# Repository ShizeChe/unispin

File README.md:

<h1 align="center">Unispin</h1>
<p align="center">A unified quantum control platform for quantum dot spin qubits</p>

Overview
========
Unispin is a unified quantum control platform designed specifically for quantum dot spin qubits. Its goal is to reduce control stack complexity and cost while improving performance by integrating all the requried control resources onto a single FPGA. With the two custom PCBs (FMC breakout board and low-noise DAC board), the current configuration has:

* 24x bias DC channels (AD5791BRUZ)
* 6x RF IQ pairs for further analog upconversion
* 2x singled-ended RF channels and 2x ADC channels for lockin-in measurement
* 2x singled-ended fast DC channels

Each signal and measurement channel has its own dedicated, fully-pipelined control core. Each core can be programmed to iteratively executes a sequence of custom assembly instructions with cycle-precise timing. The annotated pulse experiment assembly program and waveform below demonstrates this execution model.

```text
.program rf0                 # program for RF channel 0
.fnco 10MHz                  # NCO is 10MHz
.repeat 100                  # repeats 100 times
    idl t=19us (arm)         # idle for 19us
    ply phs=0 t=12ns (t+8ns) # play the NCO tone for 12ns (increment the pulse duration by 8ns every iteration)
    idl t=12us               # idle for 12us

.program dc0                 # program for DC channel 0
.repeat 100                  # this program repeats 100 times
    lvl v=0 t=2us (arm)      # output 0V for 2us
    lvl v=1 t=15us           # output 1V for 15us
    lvl v=2 t=2us            # output 2V for 2us
    idl t=12ns (t+8ns)       # idle for 12ns (increment the idle duration by 8ns every iteration)
    lvl v=1 t=10us           # output 1V for 10us
    lvl v=0 t=2us            # output 0V for 2us

.program li0                 # program for LI (lock-in) channel 0
.repeat 100                  # this program repeats 100 times
    idl t=19us (arm)         # idle for 19us
    idl t=12ns (t+8ns)       # idle for 12ns (increment the idle duration by 8ns every iteration)
    sam n=1000 t=10us        # sample 1000 samples spanning 10us
    idl t=2us                # idle for 2us

.launch rf0 dc0 li0          # launch RF channel 0, DC channel 0, LI channel 0 
```

## Project Status
The project currently has three parts:
* RTL design, along with testbenches and some formal properties used for verification (under rtl)
* PCB design for the 24 bias DC channels, along with assembly instrctions (under pcb)
* Assembler for compiling and executing the custom assembly programs (under asm)

This project is currently under active development. The RTL design, PCB design, and assembler may continue to evolve as functionality is validated experimentally and the system is further refined. More detailed documentation and user guides will be added after real-device experiments.

## Building the rtl design project and bistream in Vivado
```bash
# clone repo
git clone "repo-url"

# go to the synthesis folder
cd unispin/rtl/synth

# build in vivado
vivado -script proj.tcl &
```
Note that proj.tcl only builds the project. Click generate bitstream in vivado to build the bitstream.

## Building the simulator (requires VCS+Verdi)
This simulator is our go-to method to visualize the full-system waveforms. It incorporates all the channels and cores and have simulated DAC and ADC modules for directly visualizing analog waveforms. It simulates AXI memory operations by accepting address and data through a socket interface, the received address and data are then written to the sequencer through its AXI interface.

Build the simulator. 
```bash
# assume we are in the top level of the cloned repo

# go to the rtl folder
cd unispin/rtl

# build the simulator (requires VCS)
make
```
This will create a simulator executable under rtl.

Execute the simulator in Verdi.
```bash
./simulator -gui -do sim/wv.tcl &
```

This will open up Verdi and load the waveforms. It will listen for connections and read address and data once running. Verdi can stop it at anytime to examine waveforms.

## Building the assembler
```bash
# assume we are in the top level of the cloned repo

# go to the asm folder
cd asm

# build the assmebler
make
```
This will create an executable named "squish" under asm.

Example assembling a .asm file and send to the simulator to visualize exection (with simulator running).
```bash
./squish -s -f ../exp/hahn_echo.asm
```

## Petalinux
A Petalinux OS can be built to interface with the cores in FPGA. os/petalinux-steps.md describes the steps we took to build a bootable image with an uio driver for each core.

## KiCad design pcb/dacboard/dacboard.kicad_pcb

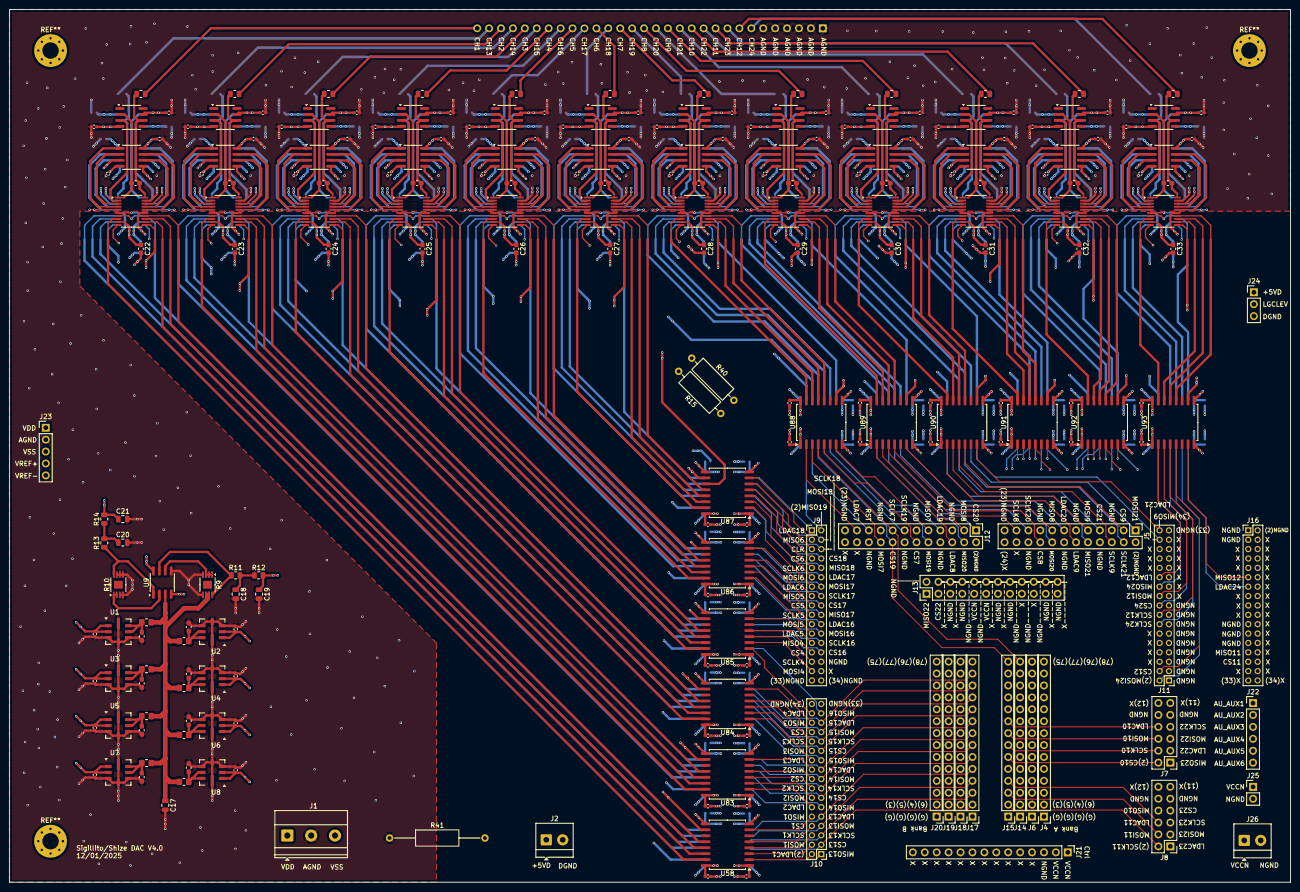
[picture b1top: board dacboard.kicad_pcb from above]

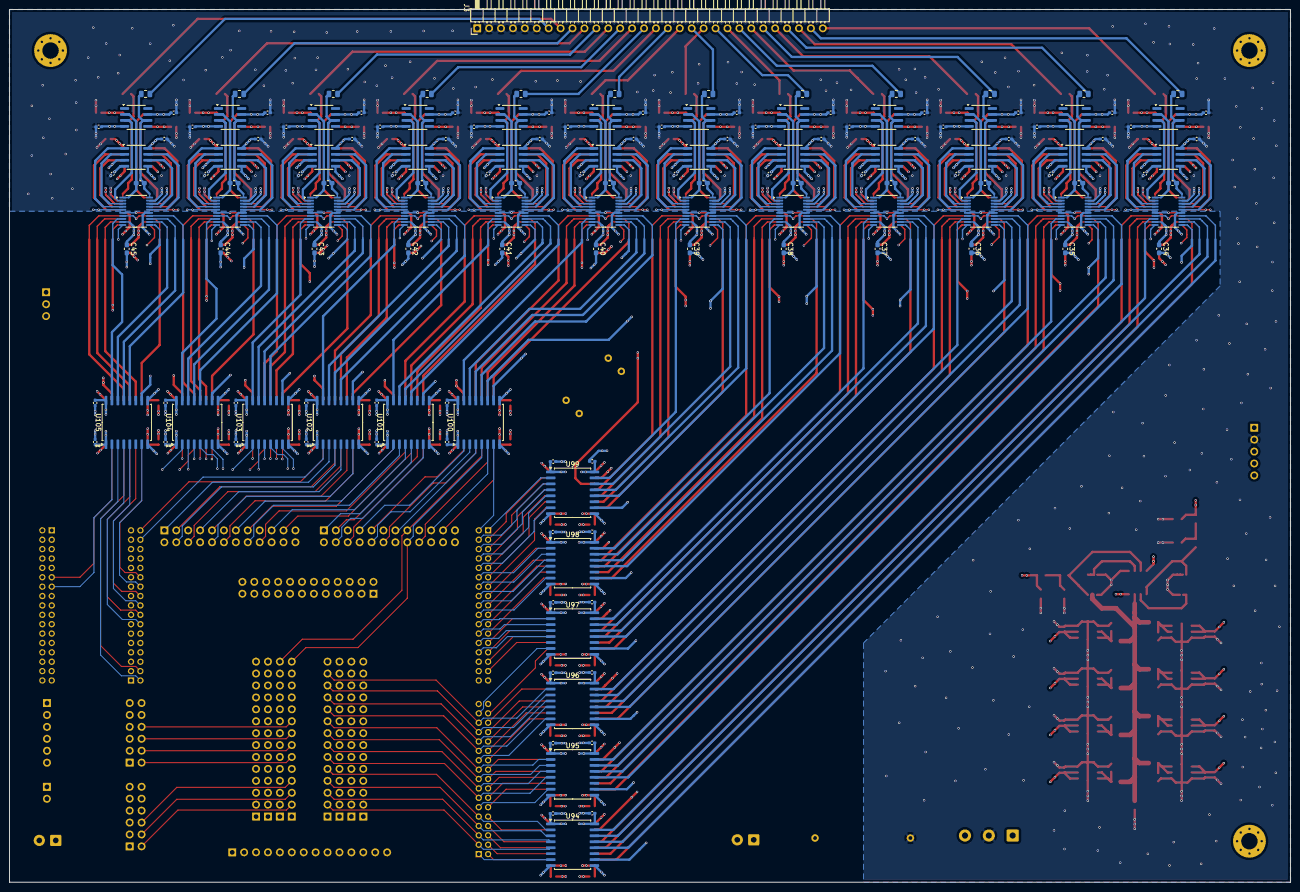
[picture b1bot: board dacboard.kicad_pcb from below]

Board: 14 copper layers, 273.0 x 186.0 mm, 385 parts (157 on the bottom side), 467 nets.

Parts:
C1, C3, C5, C7, C9, C11, C13, C15, C72, C73, C74, C75, C76, C77, C78, C79, C80, C81, C82, C83, C84, C85, C86, C87, C88, C89, C90, C91, C92, C93, C94, C95, C96, C97, C98, C99, C100, C101, C102, C103, C104, C105, C106, C107, C108, C109, C110, C111, C112, C113, C114, C115, C116, C117, C118, C119: 0.1uF; C_0402_1005Metric_Pad0.74x0.62mm_HandSolder
C2, C4, C6, C8, C10, C12, C14, C16, C22, C23, C24, C25, C26, C27, C28, C29, C30, C31, C32, C33, C34, C35, C36, C37, C38, C39, C40, C41, C42, C43, C44, C45: 10uF; C_0603_1608Metric_Pad1.08x0.95mm_HandSolder
C17, C18, C19, C20, C21: C; C_0805_2012Metric
C46, C71, C120, C121, C122, C123, C124, C125, C126, C127, C128, C129, C130, C131, C132, C133, C134, C135, C136, C137, C138, C139, C140, C141, C142, C143, C144, C145, C146, C147, C148, C149, C150, C151, C152, C153, C154, C155, C156, C157, C158, C159, C160, C161, C162, C163, C164, C165, C166, C167, C168, C169, C170, C171, C172, C173, C174, C175, C176, C177, C178, C179, C180, C181, C182, C183, C184, C185, C186, C187, C188, C189, C190, C191, C192, C193, C194, C195, C196, C197, C198, C199, C200, C201, C202, C203, C204, C205, C206, C207, C208, C209, C210, C211, C212, C213: C; C_0402_1005Metric_Pad0.74x0.62mm_HandSolder
C47, C48, C49, C50, C51, C52, C53, C54, C55, C56, C57, C58, C59, C60, C61, C62, C63, C64, C65, C66, C67, C68, C69, C70: 10pF; C_0603_1608Metric_Pad1.08x0.95mm_HandSolder
J1: Screw_Terminal_01x03; TerminalBlock_Phoenix_MKDS-1,5-3-5.08_1x03_P5.08mm_Horizont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
J2, J26: Screw_Terminal_01x02; TerminalBlock_4Ucon_1x02_P3.50mm_Horizontal
J3: Conn_01x30_Socket; PinHeader_1x30_P2.54mm_Horizontal
J4, J6, J14, J15, J17, J18, J19, J20, J21: Conn_01x14; PinHeader_1x14_P2.54mm_Vertical
J5, J12, J13: Conn_02x12_Odd_Even; PinHeader_2x12_P2.54mm_Vertical
J7, J8: Conn_02x06_Odd_Even; PinHeader_2x06_P2.54mm_Vertical
J9, J10, J11, J16: Conn_02x17_Odd_Even; PinHeader_2x17_P2.00mm_Vertical
J22: Conn_01x06; PinHeader_1x06_P2.54mm_Vertical
J23: Conn_01x05; PinHeader_1x05_P2.54mm_Vertical
J24: Conn_01x03; PinHeader_1x03_P2.54mm_Vertical
J25: Conn_01x02; PinHeader_1x02_P2.54mm_Vertical
R1, R2, R3, R4, R5, R6, R7, R8: 32.4ohm; R_0805_2012Metric_Pad1.20x1.40mm_HandSolder
R9, R10: LT5400BCMS8E-7_PBF; MSOP-8-1EP_3x3mm_P0.65mm_EP1.68x1.88mm
R11, R12, R13, R14, R16, R17, R18, R19, R20, R21, R22, R23, R24, R25, R26, R27, R28, R29, R30, R31, R32, R33, R34, R35, R36, R37, R38, R39: R_US; R_0805_2012Metric
R15, R40: R_US; R_Axial_DIN0309_L9.0mm_D3.2mm_P12.70mm_Horizontal
R41: R_US; R_Axial_DIN0309_L9.0mm_D3.2mm_P20.32mm_Horizontal
U1, U2, U3, U4, U5, U6, U7, U8: LTC6655CHMS8-2.5_PBF; Analog_LCC-8_5x5mm_P1.27mm
U9, U11, U12, U14, U16, U18, U20, U22, U23, U24, U25, U30, U31, U34, U35, U36, U37, U42, U43, U46, U47, U48, U49, U54, U55: AD8676xR; SOIC-8_3.9x4.9mm_P1.27mm
U10, U13, U15, U17, U19, U21, U26, U27, U28, U29, U32, U33, U38, U39, U40, U41, U44, U45, U50, U51, U52, U53, U56, U57: AD5791BRUZ; TSSOP-20_4.4x6.5mm_P0.65mm
U58, U83, U84, U85, U86, U87, U88, U89, U90, U91, U92, U93, U94, U95, U96, U97, U98, U99, U100, U101, U102, U103, U104, U105: ISO6761FQDWRQ1; SOIC-16W_7.5x10.3mm_P1.27mm
U59, U60, U61, U62, U63, U64, U65, U66, U67, U68, U69, U70, U71, U72, U73, U74, U75, U76, U77, U78, U79, U80, U81, U82: AD8675ARZ; SOIC-8_3.9x4.9mm_P1.27mm

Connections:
+5VD: C22.1, C23.1, C24.1, C25.1, C26.1, C27.1, C28.1, C29.1, C30.1, C31.1, C32.1, C33.1, C34.1, C35.1, C36.1, C37.1, C38.1, C39.1, C40.1, C41.1, C42.1, C43.1, C44.1, C45.1, C73.2, C75.2, C77.2, C81.2, C82.2, C83.2, C87.2, C88.2, C89.2, C93.2, C94.2, C95.2, C99.2, C100.2, C101.2, C105.2, C106.2, C107.2, C111.2, C112.2, C113.2, C117.2, C118.2, C119.2, J2.1, J24.1, R15.1, U10.9 (VCC), U13.9 (VCC), U15.9 (VCC), U17.9 (VCC), U19.9 (VCC), U21.9 (VCC), U26.9 (VCC), U27.9 (VCC), U28.9 (VCC), U29.9 (VCC), U32.9 (VCC), U33.9 (VCC), U38.9 (VCC), U39.9 (VCC), U40.9 (VCC), U41.9 (VCC), U44.9 (VCC), U45.9 (VCC), U50.9 (VCC), U51.9 (VCC), U52.9 (VCC), U53.9 (VCC), U56.9 (VCC), U57.9 (VCC), U58.16 (VCC2), U83.16 (VCC2), U84.16 (VCC2), U85.16 (VCC2), U86.16 (VCC2), U87.16 (VCC2), U88.16 (VCC2), U89.16 (VCC2), U90.16 (VCC2), U91.16 (VCC2), U92.16 (VCC2), U93.16 (VCC2), U94.16 (VCC2), U95.16 (VCC2), U96.16 (VCC2), U97.16 (VCC2), U98.16 (VCC2), U99.16 (VCC2), U100.16 (VCC2), U101.16 (VCC2), U102.16 (VCC2), U103.16 (VCC2), U104.16 (VCC2), U105.16 (VCC2)
AGND: C1.2, C2.2, C3.2, C4.2, C5.2, C6.2, C7.2, C8.2, C9.2, C10.2, C11.2, C12.2, C13.2, C14.2, C15.2, C16.2, C17.2, C18.2, C19.2, C20.2, C21.2, C46.2, C71.2, C120.2, C121.2, C122.2, C123.2, C124.2, C125.2, C126.2, C127.2, C128.2, C129.2, C130.2, C131.2, C132.2, C133.2, C134.2, C135.2, C136.2, C137.2, C138.2, C139.2, C140.2, C141.2, C142.2, C143.2, C144.2, C145.2, C146.2, C147.2, C148.2, C149.2, C150.2, C151.2, C152.2, C153.2, C154.2, C155.2, C156.2, C157.2, C158.2, C159.2, C160.2, C161.2, C162.2, C163.2, C164.2, C165.2, C166.2, C167.2, C168.2, C169.2, C170.2, C171.2, C172.2, C173.2, C174.2, C175.2, C176.2, C177.2, C178.2, C179.2, C180.2, C181.2, C182.2, C183.2, C184.2, C185.2, C186.2, C187.2, C188.2, C189.2, C190.2, C191.2, C192.2, C193.2, C194.2, C195.2, C196.2, C197.2, C198.2, C199.2, C200.2, C201.2, C202.2, C203.2, C204.2, C205.2, C206.2, C207.2, C208.2, C209.2, C210.2, C211.2, C212.2, C213.2, J1.2, J3.1, J3.2, J3.3, J3.4, J3.5, J3.6, J23.2, R9.4, R9.5, R10.3, R10.4, R10.5, R10.6, R10.7, R41.1, U1.3 (GND), U1.4 (GND__1), U1.5 (GND__2), U1.8 (GND__3), U2.3 (GND), U2.4 (GND__1), U2.5 (GND__2), U2.8 (GND__3), U3.3 (GND), U3.4 (GND__1), U3.5 (GND__2), U3.8 (GND__3), U4.3 (GND), U4.4 (GND__1), U4.5 (GND__2), U4.8 (GND__3), U5.3 (GND), U5.4 (GND__1), U5.5 (GND__2), U5.8 (GND__3), U6.3 (GND), U6.4 (GND__1), U6.5 (GND__2), U6.8 (GND__3), U7.3 (GND), U7.4 (GND__1), U7.5 (GND__2), U7.8 (GND__3), U8.3 (GND), U8.4 (GND__1), U8.5 (GND__2), U8.8 (GND__3), U9.5 (+), U10.19 (AGND), U13.19 (AGND), U15.19 (AGND), U17.19 (AGND), U19.19 (AGND), U21.19 (AGND), U26.19 (AGND), U27.19 (AGND), U28.19 (AGND), U29.19 (AGND), U32.19 (AGND), U33.19 (AGND), U38.19 (AGND), U39.19 (AGND), U40.19 (AGND), U41.19 (AGND), U44.19 (AGND), U45.19 (AGND), U50.19 (AGND), U51.19 (AGND), U52.19 (AGND), U53.19 (AGND), U56.19 (AGND), U57.19 (AGND)
AU_AUX1: J14.6, J22.1
AU_AUX2: J15.5, J22.2
AU_AUX3: J4.5, J22.3
AU_AUX4: J4.4, J22.4
AU_AUX5: J4.3, J22.5
AU_AUX6: J4.2, J22.6
BUF1_VOUT: J3.30, R16.2
BUF2_VOUT: J3.28, R17.2
BUF3_VOUT: J3.26, R18.2
BUF4_VOUT: J3.24, R19.2
BUF5_VOUT: J3.22, R20.2
BUF6_VOUT: J3.20, R21.2
BUF7_VOUT: J3.18, R22.2
BUF8_VOUT: J3.16, R23.2
BUF9_VOUT: J3.14, R24.2
BUF10_VOUT: J3.12, R25.2
BUF11_VOUT: J3.10, R26.2
BUF12_VOUT: J3.8, R27.2
BUF13_VOUT: J3.29, R28.2
BUF14_VOUT: J3.27, R29.2
BUF15_VOUT: J3.25, R30.2
BUF16_VOUT: J3.23, R31.2
BUF17_VOUT: J3.21, R32.2
BUF18_VOUT: J3.19, R33.2
BUF19_VOUT: J3.17, R34.2
BUF20_VOUT: J3.15, R35.2
BUF21_VOUT: J3.13, R36.2
BUF22_VOUT: J3.11, R37.2
BUF23_VOUT: J3.9, R38.2
BUF24_VOUT: J3.7, R39.2
CLR_N: U10.7 (*CLR), U13.7 (*CLR), U15.7 (*CLR), U17.7 (*CLR), U19.7 (*CLR), U21.7 (*CLR), U26.7 (*CLR), U27.7 (*CLR), U28.7 (*CLR), U29.7 (*CLR), U32.7 (*CLR), U33.7 (*CLR), U38.7 (*CLR), U39.7 (*CLR), U40.7 (*CLR), U41.7 (*CLR), U44.7 (*CLR), U45.7 (*CLR), U50.7 (*CLR), U51.7 (*CLR), U52.7 (*CLR), U53.7 (*CLR), U56.7 (*CLR), U57.7 (*CLR), U87.11 (OUTE)
CLR_N_ALLCH: J9.5, J20.13, U87.6 (INE)
CS_N_CH1: J10.8, J18.5, U58.5 (IND)
CS_N_CH2: J10.18, J18.9, U83.5 (IND)
CS_N_CH3: J10.28, J18.13, U84.5 (IND)
CS_N_CH4: J9.27, J20.4, U85.5 (IND)
CS_N_CH5: J9.17, J20.8, U86.5 (IND)
CS_N_CH6: J9.7, J20.12, U87.5 (IND)
CS_N_CH7: J4.14, J12.12, U88.5 (IND)
CS_N_CH8: J5.18, J15.11, U89.5 (IND)
CS_N_CH9: J4.9, J5.3, U90.5 (IND)
CS_N_CH10: J7.2, J15.6, U91.5 (IND)
CS_N_CH11: J4.6, J16.29, U92.5 (IND)
CS_N_CH12: J6.3, J11.4, U93.5 (IND)
CS_N_CH13: J10.3, J17.2, U94.5 (IND)
CS_N_CH14: J10.13, J17.6, U95.5 (IND)
CS_N_CH15: J10.23, J17.10, U96.5 (IND)
CS_N_CH16: J9.28, J19.2, U97.5 (IND)
CS_N_CH17: J9.18, J19.6, U98.5 (IND)
CS_N_CH18: J9.8, J19.10, U99.5 (IND)
CS_N_CH19: J12.16, J15.14, U100.5 (IND)
CS_N_CH20: J12.1, J14.12, U101.5 (IND)
CS_N_CH21: J5.7, J14.10, U102.5 (IND)
CS_N_CH22: J13.3, J14.13, U103.5 (IND)
CS_N_CH23: J8.7, J14.5, U104.5 (IND)
CS_N_CH24: J6.6, J11.18, U105.5 (IND)
DAC1_INV: C47.1, U10.1 (INV), U59.2 (IN-)
DAC1_LDAC_N: U10.8 (*LDAC), U58.15 (OUTA)
DAC1_RFB: C47.2, R16.1, U10.20 (RFB), U59.6 (OUT)
DAC1_SCLK: U10.13 (SCLK), U58.13 (OUTC)
DAC1_SDIN: U10.12 (SDIN), U58.14 (OUTB)
DAC1_SDO: U10.11 (SDO), U58.10 (INF)
DAC1_SYNC_N: U10.14 (*SYNC), U58.12 (OUTD)
DAC1_VOUT: U10.2 (VOUT), U59.3 (IN+)
DAC2_INV: C48.1, U13.1 (INV), U60.2 (IN-)
DAC2_LDAC_N: U13.8 (*LDAC), U83.15 (OUTA)
DAC2_RFB: C48.2, R17.1, U13.20 (RFB), U60.6 (OUT)
DAC2_SCLK: U13.13 (SCLK), U83.13 (OUTC)
DAC2_SDIN: U13.12 (SDIN), U83.14 (OUTB)
DAC2_SDO: U13.11 (SDO), U83.10 (INF)
DAC2_SYNC_N: U13.14 (*SYNC), U83.12 (OUTD)
DAC2_VOUT: U13.2 (VOUT), U60.3 (IN+)
DAC3_INV: C49.1, U15.1 (INV), U61.2 (IN-)
DAC3_LDAC_N: U15.8 (*LDAC), U84.15 (OUTA)
DAC3_RFB: C49.2, R18.1, U15.20 (RFB), U61.6 (OUT)
DAC3_SCLK: U15.13 (SCLK), U84.13 (OUTC)
DAC3_SDIN: U15.12 (SDIN), U84.14 (OUTB)
DAC3_SDO: U15.11 (SDO), U84.10 (INF)
DAC3_SYNC_N: U15.14 (*SYNC), U84.12 (OUTD)
DAC3_VOUT: U15.2 (VOUT), U61.3 (IN+)
DAC4_INV: C50.1, U17.1 (INV), U62.2 (IN-)
DAC4_LDAC_N: U17.8 (*LDAC), U85.15 (OUTA)
DAC4_RFB: C50.2, R19.1, U17.20 (RFB), U62.6 (OUT)
DAC4_SCLK: U17.13 (SCLK), U85.13 (OUTC)
DAC4_SDIN: U17.12 (SDIN), U85.14 (OUTB)
DAC4_SDO: U17.11 (SDO), U85.10 (INF)
DAC4_SYNC_N: U17.14 (*SYNC), U85.12 (OUTD)
DAC4_VOUT: U17.2 (VOUT), U62.3 (IN+)
DAC5_INV: C51.1, U19.1 (INV), U63.2 (IN-)
DAC5_LDAC_N: U19.8 (*LDAC), U86.15 (OUTA)
DAC5_RFB: C51.2, R20.1, U19.20 (RFB), U63.6 (OUT)
DAC5_SCLK: U19.13 (SCLK), U86.13 (OUTC)
DAC5_SDIN: U19.12 (SDIN), U86.14 (OUTB)
DAC5_SDO: U19.11 (SDO), U86.10 (INF)
DAC5_SYNC_N: U19.14 (*SYNC), U86.12 (OUTD)
DAC5_VOUT: U19.2 (VOUT), U63.3 (IN+)
DAC6_INV: C52.1, U21.1 (INV), U64.2 (IN-)
DAC6_LDAC_N: U21.8 (*LDAC), U87.15 (OUTA)
DAC6_RFB: C52.2, R21.1, U21.20 (RFB), U64.6 (OUT)
DAC6_SCLK: U21.13 (SCLK), U87.13 (OUTC)
DAC6_SDIN: U21.12 (SDIN), U87.14 (OUTB)
DAC6_SDO: U21.11 (SDO), U87.10 (INF)
DAC6_SYNC_N: U21.14 (*SYNC), U87.12 (OUTD)
DAC6_VOUT: U21.2 (VOUT), U64.3 (IN+)
DAC7_INV: C53.1, U26.1 (INV), U65.2 (IN-)
DAC7_LDAC_N: U26.8 (*LDAC), U88.15 (OUTA)
DAC7_RFB: C53.2, R22.1, U26.20 (RFB), U65.6 (OUT)
DAC7_SCLK: U26.13 (SCLK), U88.13 (OUTC)
DAC7_SDIN: U26.12 (SDIN), U88.14 (OUTB)
DAC7_SDO: U26.11 (SDO), U88.10 (INF)
DAC7_SYNC_N: U26.14 (*SYNC), U88.12 (OUTD)
DAC7_VOUT: U26.2 (VOUT), U65.3 (IN+)
DAC8_INV: C54.1, U27.1 (INV), U66.2 (IN-)
DAC8_LDAC_N: U27.8 (*LDAC), U89.15 (OUTA)
DAC8_RFB: C54.2, R23.1, U27.20 (RFB), U66.6 (OUT)
DAC8_SCLK: U27.13 (SCLK), U89.13 (OUTC)
DAC8_SDIN: U27.12 (SDIN), U89.14 (OUTB)
DAC8_SDO: U27.11 (SDO), U89.10 (INF)
DAC8_SYNC_N: U27.14 (*SYNC), U89.12 (OUTD)
DAC8_VOUT: U27.2 (VOUT), U66.3 (IN+)
DAC9_INV: C55.1, U28.1 (INV), U67.2 (IN-)
DAC9_LDAC_N: U28.8 (*LDAC), U90.15 (OUTA)
DAC9_RFB: C55.2, R24.1, U28.20 (RFB), U67.6 (OUT)
DAC9_SCLK: U28.13 (SCLK), U90.13 (OUTC)
DAC9_SDIN: U28.12 (SDIN), U90.14 (OUTB)
DAC9_SDO: U28.11 (SDO), U90.10 (INF)
DAC9_SYNC_N: U28.14 (*SYNC), U90.12 (OUTD)
DAC9_VOUT: U28.2 (VOUT), U67.3 (IN+)
DAC10_INV: C56.1, U29.1 (INV), U68.2 (IN-)
DAC10_LDAC_N: U29.8 (*LDAC), U91.15 (OUTA)
DAC10_RFB: C56.2, R25.1, U29.20 (RFB), U68.6 (OUT)
DAC10_SCLK: U29.13 (SCLK), U91.13 (OUTC)
DAC10_SDIN: U29.12 (SDIN), U91.14 (OUTB)
DAC10_SDO: U29.11 (SDO), U91.10 (INF)
DAC10_SYNC_N: U29.14 (*SYNC), U91.12 (OUTD)
DAC10_VOUT: U29.2 (VOUT), U68.3 (IN+)
DAC11_INV: C57.1, U32.1 (INV), U69.2 (IN-)
DAC11_LDAC_N: U32.8 (*LDAC), U92.15 (OUTA)
DAC11_RFB: C57.2, R26.1, U32.20 (RFB), U69.6 (OUT)
DAC11_SCLK: U32.13 (SCLK), U92.13 (OUTC)
DAC11_SDIN: U32.12 (SDIN), U92.14 (OUTB)
DAC11_SDO: U32.11 (SDO), U92.10 (INF)
DAC11_SYNC_N: U32.14 (*SYNC), U92.12 (OUTD)
DAC11_VOUT: U32.2 (VOUT), U69.3 (IN+)
DAC12_INV: C58.1, U33.1 (INV), U70.2 (IN-)
DAC12_LDAC_N: U33.8 (*LDAC), U93.15 (OUTA)
DAC12_RFB: C58.2, R27.1, U33.20 (RFB), U70.6 (OUT)
DAC12_SCLK: U33.13 (SCLK), U93.13 (OUTC)
DAC12_SDIN: U33.12 (SDIN), U93.14 (OUTB)
DAC12_SDO: U33.11 (SDO), U93.10 (INF)
DAC12_SYNC_N: U33.14 (*SYNC), U93.12 (OUTD)
DAC12_VOUT: U33.2 (VOUT), U70.3 (IN+)
DAC13_INV: C59.1, U38.1 (INV), U71.2 (IN-)
DAC13_LDAC_N: U38.8 (*LDAC), U94.15 (OUTA)
DAC13_RFB: C59.2, R28.1, U38.20 (RFB), U71.6 (OUT)
DAC13_SCLK: U38.13 (SCLK), U94.13 (OUTC)
DAC13_SDIN: U38.12 (SDIN), U94.14 (OUTB)
DAC13_SDO: U38.11 (SDO), U94.10 (INF)
DAC13_SYNC_N: U38.14 (*SYNC), U94.12 (OUTD)
DAC13_VOUT: U38.2 (VOUT), U71.3 (IN+)
DAC14_INV: C60.1, U39.1 (INV), U72.2 (IN-)
DAC14_LDAC_N: U39.8 (*LDAC), U95.15 (OUTA)
DAC14_RFB: C60.2, R29.1, U39.20 (RFB), U72.6 (OUT)
DAC14_SCLK: U39.13 (SCLK), U95.13 (OUTC)
DAC14_SDIN: U39.12 (SDIN), U95.14 (OUTB)
DAC14_SDO: U39.11 (SDO), U95.10 (INF)
DAC14_SYNC_N: U39.14 (*SYNC), U95.12 (OUTD)
DAC14_VOUT: U39.2 (VOUT), U72.3 (IN+)
DAC15_INV: C61.1, U40.1 (INV), U73.2 (IN-)
DAC15_LDAC_N: U40.8 (*LDAC), U96.15 (OUTA)
DAC15_RFB: C61.2, R30.1, U40.20 (RFB), U73.6 (OUT)
DAC15_SCLK: U40.13 (SCLK), U96.13 (OUTC)
DAC15_SDIN: U40.12 (SDIN), U96.14 (OUTB)
DAC15_SDO: U40.11 (SDO), U96.10 (INF)
DAC15_SYNC_N: U40.14 (*SYNC), U96.12 (OUTD)
DAC15_VOUT: U40.2 (VOUT), U73.3 (IN+)
DAC16_INV: C62.1, U41.1 (INV), U74.2 (IN-)
DAC16_LDAC_N: U41.8 (*LDAC), U97.15 (OUTA)
DAC16_RFB: C62.2, R31.1, U41.20 (RFB), U74.6 (OUT)
DAC16_SCLK: U41.13 (SCLK), U97.13 (OUTC)
DAC16_SDIN: U41.12 (SDIN), U97.14 (OUTB)
DAC16_SDO: U41.11 (SDO), U97.10 (INF)
DAC16_SYNC_N: U41.14 (*SYNC), U97.12 (OUTD)
DAC16_VOUT: U41.2 (VOUT), U74.3 (IN+)
DAC17_INV: C63.1, U44.1 (INV), U75.2 (IN-)
DAC17_LDAC_N: U44.8 (*LDAC), U98.15 (OUTA)
DAC17_RFB: C63.2, R32.1, U44.20 (RFB), U75.6 (OUT)
DAC17_SCLK: U44.13 (SCLK), U98.13 (OUTC)
DAC17_SDIN: U44.12 (SDIN), U98.14 (OUTB)
DAC17_SDO: U44.11 (SDO), U98.10 (INF)
DAC17_SYNC_N: U44.14 (*SYNC), U98.12 (OUTD)
DAC17_VOUT: U44.2 (VOUT), U75.3 (IN+)
DAC18_INV: C64.1, U45.1 (INV), U76.2 (IN-)
DAC18_LDAC_N: U45.8 (*LDAC), U99.15 (OUTA)
DAC18_RFB: C64.2, R33.1, U45.20 (RFB), U76.6 (OUT)
DAC18_SCLK: U45.13 (SCLK), U99.13 (OUTC)
DAC18_SDIN: U45.12 (SDIN), U99.14 (OUTB)
DAC18_SDO: U45.11 (SDO), U99.10 (INF)
DAC18_SYNC_N: U45.14 (*SYNC), U99.12 (OUTD)
DAC18_VOUT: U45.2 (VOUT), U76.3 (IN+)
DAC19_INV: C65.1, U50.1 (INV), U77.2 (IN-)
DAC19_LDAC_N: U50.8 (*LDAC), U100.15 (OUTA)
DAC19_RFB: C65.2, R34.1, U50.20 (RFB), U77.6 (OUT)
DAC19_SCLK: U50.13 (SCLK), U100.13 (OUTC)
DAC19_SDIN: U50.12 (SDIN), U100.14 (OUTB)
DAC19_SDO: U50.11 (SDO), U100.10 (INF)
DAC19_SYNC_N: U50.14 (*SYNC), U100.12 (OUTD)
DAC19_VOUT: U50.2 (VOUT), U77.3 (IN+)
DAC20_INV: C66.1, U51.1 (INV), U78.2 (IN-)
DAC20_LDAC_N: U51.8 (*LDAC), U101.15 (OUTA)
DAC20_RFB: C66.2, R35.1, U51.20 (RFB), U78.6 (OUT)
DAC20_SCLK: U51.13 (SCLK), U101.13 (OUTC)
DAC20_SDIN: U51.12 (SDIN), U101.14 (OUTB)
DAC20_SDO: U51.11 (SDO), U101.10 (INF)
DAC20_SYNC_N: U51.14 (*SYNC), U101.12 (OUTD)
DAC20_VOUT: U51.2 (VOUT), U78.3 (IN+)
DAC21_INV: C67.1, U52.1 (INV), U79.2 (IN-)
DAC21_LDAC_N: U52.8 (*LDAC), U102.15 (OUTA)
DAC21_RFB: C67.2, R36.1, U52.20 (RFB), U79.6 (OUT)
DAC21_SCLK: U52.13 (SCLK), U102.13 (OUTC)
DAC21_SDIN: U52.12 (SDIN), U102.14 (OUTB)
DAC21_SDO: U52.11 (SDO), U102.10 (INF)
DAC21_SYNC_N: U52.14 (*SYNC), U102.12 (OUTD)
DAC21_VOUT: U52.2 (VOUT), U79.3 (IN+)
DAC22_INV: C68.1, U53.1 (INV), U80.2 (IN-)
DAC22_LDAC_N: U53.8 (*LDAC), U103.15 (OUTA)
DAC22_RFB: C68.2, R37.1, U53.20 (RFB), U80.6 (OUT)
DAC22_SCLK: U53.13 (SCLK), U103.13 (OUTC)
DAC22_SDIN: U53.12 (SDIN), U103.14 (OUTB)
DAC22_SDO: U53.11 (SDO), U103.10 (INF)
DAC22_SYNC_N: U53.14 (*SYNC), U103.12 (OUTD)
DAC22_VOUT: U53.2 (VOUT), U80.3 (IN+)
DAC23_INV: C69.1, U56.1 (INV), U81.2 (IN-)
DAC23_LDAC_N: U56.8 (*LDAC), U104.15 (OUTA)
DAC23_RFB: C69.2, R38.1, U56.20 (RFB), U81.6 (OUT)
DAC23_SCLK: U56.13 (SCLK), U104.13 (OUTC)
DAC23_SDIN: U56.12 (SDIN), U104.14 (OUTB)
DAC23_SDO: U56.11 (SDO), U104.10 (INF)
DAC23_SYNC_N: U56.14 (*SYNC), U104.12 (OUTD)
DAC23_VOUT: U56.2 (VOUT), U81.3 (IN+)
DAC24_INV: C70.1, U57.1 (INV), U82.2 (IN-)
DAC24_LDAC_N: U57.8 (*LDAC), U105.15 (OUTA)
DAC24_RFB: C70.2, R39.1, U57.20 (RFB), U82.6 (OUT)
DAC24_SCLK: U57.13 (SCLK), U105.13 (OUTC)
DAC24_SDIN: U57.12 (SDIN), U105.14 (OUTB)
DAC24_SDO: U57.11 (SDO), U105.10 (INF)
DAC24_SYNC_N: U57.14 (*SYNC), U105.12 (OUTD)
DAC24_VOUT: U57.2 (VOUT), U82.3 (IN+)
DGND: C22.2, C23.2, C24.2, C25.2, C26.2, C27.2, C28.2, C29.2, C30.2, C31.2, C32.2, C33.2, C34.2, C35.2, C36.2, C37.2, C38.2, C39.2, C40.2, C41.2, C42.2, C43.2, C44.2, C45.2, C73.1, C75.1, C77.1, C81.1, C82.1, C83.1, C87.1, C88.1, C89.1, C93.1, C94.1, C95.1, C99.1, C100.1, C101.1, C105.1, C106.1, C107.1, C111.1, C112.1, C113.1, C117.1, C118.1, C119.1, J2.2, J24.3, R40.2, R41.2, U10.15 (DGND), U13.15 (DGND), U15.15 (DGND), U17.15 (DGND), U19.15 (DGND), U21.15 (DGND), U26.15 (DGND), U27.15 (DGND), U28.15 (DGND), U29.15 (DGND), U32.15 (DGND), U33.15 (DGND), U38.15 (DGND), U39.15 (DGND), U40.15 (DGND), U41.15 (DGND), U44.15 (DGND), U45.15 (DGND), U50.15 (DGND), U51.15 (DGND), U52.15 (DGND), U53.15 (DGND), U56.15 (DGND), U57.15 (DGND), U58.9 (GND2), U83.9 (GND2), U84.9 (GND2), U85.9 (GND2), U86.9 (GND2), U87.9 (GND2), U88.9 (GND2), U89.9 (GND2), U90.9 (GND2), U91.9 (GND2), U92.9 (GND2), U93.9 (GND2), U94.9 (GND2), U95.9 (GND2), U96.9 (GND2), U97.9 (GND2), U98.9 (GND2), U99.9 (GND2), U100.9 (GND2), U101.9 (GND2), U102.9 (GND2), U103.9 (GND2), U104.9 (GND2), U105.9 (GND2)
LDAC_N_CH1: J10.2, J18.2, U58.2 (INA)
LDAC_N_CH2: J10.12, J18.6, U83.2 (INA)
LDAC_N_CH3: J10.22, J18.10, U84.2 (INA)
LDAC_N_CH4: J10.32, J17.14, U85.2 (INA)
LDAC_N_CH5: J9.23, J20.5, U86.2 (INA)
LDAC_N_CH6: J9.13, J20.9, U87.2 (INA)
LDAC_N_CH7: J12.21, J20.14, U88.2 (INA)
LDAC_N_CH8: J4.13, J12.6, U89.2 (INA)
LDAC_N_CH9: J4.11, J5.12, U90.2 (INA)
LDAC_N_CH10: J7.8, J15.9, U91.2 (INA)
LDAC_N_CH11: J8.6, J15.4, U92.2 (INA)
LDAC_N_CH12: J6.8, J11.24, U93.2 (INA)
LDAC_N_CH13: J10.9, J17.5, U94.2 (INA)
LDAC_N_CH14: J10.19, J17.9, U95.2 (INA)
LDAC_N_CH15: J10.29, J17.13, U96.2 (INA)
LDAC_N_CH16: J9.22, J19.5, U97.2 (INA)
LDAC_N_CH17: J9.12, J19.9, U98.2 (INA)
LDAC_N_CH18: J9.1, J19.13, U99.2 (INA)
LDAC_N_CH19: J6.13, J12.7, U100.2 (INA)
LDAC_N_CH20: J5.13, J6.11, U101.2 (INA)
LDAC_N_CH21: J6.9, J11.32, U102.2 (INA)
LDAC_N_CH22: J7.3, J14.7, U103.2 (INA)
LDAC_N_CH23: J8.1, J14.2, U104.2 (INA)
LDAC_N_CH24: J4.7, J16.13, U105.2 (INA)
LOGIC_LEVEL: J24.2, R15.2, R40.1, U10.10 (IOVCC), U13.10 (IOVCC), U15.10 (IOVCC), U17.10 (IOVCC), U19.10 (IOVCC), U21.10 (IOVCC), U26.10 (IOVCC), U27.10 (IOVCC), U28.10 (IOVCC), U29.10 (IOVCC), U32.10 (IOVCC), U33.10 (IOVCC), U38.10 (IOVCC), U39.10 (IOVCC), U40.10 (IOVCC), U41.10 (IOVCC), U44.10 (IOVCC), U45.10 (IOVCC), U50.10 (IOVCC), U51.10 (IOVCC), U52.10 (IOVCC), U53.10 (IOVCC), U56.10 (IOVCC), U57.10 (IOVCC)
MISO_CH1: J10.10, U58.7 (OUTF)
MISO_CH2: J10.20, U83.7 (OUTF)
MISO_CH3: J10.30, U84.7 (OUTF)
MISO_CH4: J9.25, U85.7 (OUTF)
MISO_CH5: J9.15, U86.7 (OUTF)
MISO_CH6: J9.3, U87.7 (OUTF)
MISO_CH7: J12.9, U88.7 (OUTF)
MISO_CH8: J5.15, U89.7 (OUTF)
MISO_CH9: J11.34, U90.7 (OUTF)
MISO_CH10: J8.8, U91.7 (OUTF)
MISO_CH11: J16.27, U92.7 (OUTF)
MISO_CH12: J16.11, U93.7 (OUTF)
MISO_CH13: J10.1, U94.7 (OUTF)
MISO_CH14: J10.11, U95.7 (OUTF)
MISO_CH15: J10.21, U96.7 (OUTF)
MISO_CH16: J10.31, U97.7 (OUTF)
MISO_CH17: J9.20, U98.7 (OUTF)
MISO_CH18: J9.10, U99.7 (OUTF)
MISO_CH19: J9.2, U100.7 (OUTF)
MISO_CH20: J12.4, U101.7 (OUTF)
MISO_CH21: J5.10, U102.7 (OUTF)
MISO_CH22: J13.1, U103.7 (OUTF)
MISO_CH23: J7.1, U104.7 (OUTF)
MISO_CH24: J11.22, U105.7 (OUTF)
MOSI_CH1: J10.4, J18.3, U58.3 (INB)
MOSI_CH2: J10.14, J18.7, U83.3 (INB)
MOSI_CH3: J10.24, J18.11, U84.3 (INB)
MOSI_CH4: J9.31, J20.2, U85.3 (INB)
MOSI_CH5: J9.21, J20.6, U86.3 (INB)
MOSI_CH6: J9.11, J20.10, U87.3 (INB)
MOSI_CH7: J12.18, J18.14, U88.3 (INB)
MOSI_CH8: J12.3, J15.12, U89.3 (INB)
MOSI_CH9: J5.9, J15.10, U90.3 (INB)
MOSI_CH10: J7.6, J15.8, U91.3 (INB)
MOSI_CH11: J8.4, J15.3, U92.3 (INB)
MOSI_CH12: J6.7, J11.20, U93.3 (INB)
MOSI_CH13: J10.7, J17.4, U94.3 (INB)
MOSI_CH14: J10.17, J17.8, U95.3 (INB)
MOSI_CH15: J10.27, J17.12, U96.3 (INB)
MOSI_CH16: J9.24, J19.4, U97.3 (INB)
MOSI_CH17: J9.14, J19.8, U98.3 (INB)
MOSI_CH18: J9.4, J19.12, U99.3 (INB)
MOSI_CH19: J12.10, J15.13, U100.3 (INB)
MOSI_CH20: J5.16, J14.11, U101.3 (INB)
MOSI_CH21: J4.8, J5.1, U102.3 (INB)
MOSI_CH22: J7.5, J14.8, U103.3 (INB)
MOSI_CH23: J8.3, J14.3, U104.3 (INB)
MOSI_CH24: J6.2, J11.2, U105.3 (INB)
NGND: C72.1, C74.1, C76.1, C78.1, C79.1, C80.1, C84.1, C85.1, C86.1, C90.1, C91.1, C92.1, C96.1, C97.1, C98.1, C102.1, C103.1, C104.1, C108.1, C109.1, C110.1, C114.1, C115.1, C116.1, J4.1, J5.2, J5.5, J5.8, J5.11, J5.14, J5.17, J5.20, J5.23, J6.1, J7.9, J7.10, J8.9, J8.10, J9.30, J9.33, J9.34, J10.33, J10.34, J11.1, J11.3, J11.5, J11.7, J11.9, J11.11, J11.13, J11.15, J11.17, J11.33, J12.2, J12.5, J12.8, J12.11, J12.14, J12.17, J12.20, J12.23, J13.2, J13.5, J13.7, J13.8, J13.10, J13.13, J13.15, J13.16, J13.18, J13.20, J13.21, J13.23, J14.1, J15.1, J16.1, J16.2, J16.3, J16.21, J16.23, J16.25, J17.1, J18.1, J19.1, J20.1, J21.3, J25.2, J26.2, U58.8 (GND1), U83.8 (GND1), U84.8 (GND1), U85.8 (GND1), U86.8 (GND1), U87.8 (GND1), U88.8 (GND1), U89.8 (GND1), U90.8 (GND1), U91.8 (GND1), U92.8 (GND1), U93.8 (GND1), U94.8 (GND1), U95.8 (GND1), U96.8 (GND1), U97.8 (GND1), U98.8 (GND1), U99.8 (GND1), U100.8 (GND1), U101.8 (GND1), U102.8 (GND1), U103.8 (GND1), U104.8 (GND1), U105.8 (GND1)
unnamed: C18.1, R11.2, R12.1
unnamed: C20.1, R13.2, R14.1
unnamed: R10.8, R13.1, U9.1
unnamed: R9.8, R11.1, U9.7
unnamed: C17.1, R1.2, R2.2, R3.2, R4.2, R5.2, R6.2, R7.2, R8.2, R9.6, R9.7, U9.3 (+)
unnamed: R10.1, R10.2, U9.2 (-)
unnamed: R9.1, R9.2, R9.3, U9.6 (-)
unnamed: U10.16 (VREFNF), U11.7
unnamed: U10.17 (VREFNS), U11.6 (-)
unnamed: U10.4 (VREFPF), U11.1
unnamed: U10.3 (VREFPS), U11.2 (-)
unnamed: U12.2 (-), U13.3 (VREFPS)
unnamed: U12.6 (-), U13.17 (VREFNS)
unnamed: U12.7, U13.16 (VREFNF)
unnamed: U12.1, U13.4 (VREFPF)
unnamed: U14.2 (-), U15.3 (VREFPS)
unnamed: U14.6 (-), U15.17 (VREFNS)
unnamed: U14.7, U15.16 (VREFNF)
unnamed: U14.1, U15.4 (VREFPF)
unnamed: U16.2 (-), U17.3 (VREFPS)
unnamed: U16.6 (-), U17.17 (VREFNS)
unnamed: U16.7, U17.16 (VREFNF)
unnamed: U16.1, U17.4 (VREFPF)
unnamed: U18.2 (-), U19.3 (VREFPS)
unnamed: U18.6 (-), U19.17 (VREFNS)
unnamed: U18.7, U19.16 (VREFNF)
unnamed: U18.1, U19.4 (VREFPF)
unnamed: U20.2 (-), U21.3 (VREFPS)
unnamed: U20.6 (-), U21.17 (VREFNS)
unnamed: U20.7, U21.16 (VREFNF)
unnamed: U20.1, U21.4 (VREFPF)
unnamed: U22.2 (-), U26.3 (VREFPS)
unnamed: U22.6 (-), U26.17 (VREFNS)
unnamed: U23.2 (-), U27.3 (VREFPS)
unnamed: U23.6 (-), U27.17 (VREFNS)
unnamed: U24.2 (-), U28.3 (VREFPS)
unnamed: U24.6 (-), U28.17 (VREFNS)
unnamed: U25.2 (-), U29.3 (VREFPS)
unnamed: U25.6 (-), U29.17 (VREFNS)
unnamed: U22.7, U26.16 (VREFNF)
unnamed: U22.1, U26.4 (VREFPF)
unnamed: U23.7, U27.16 (VREFNF)
unnamed: U23.1, U27.4 (VREFPF)
unnamed: U24.7, U28.16 (VREFNF)
unnamed: U24.1, U28.4 (VREFPF)
unnamed: U25.7, U29.16 (VREFNF)
unnamed: U25.1, U29.4 (VREFPF)
unnamed: U30.2 (-), U32.3 (VREFPS)
unnamed: U30.6 (-), U32.17 (VREFNS)
unnamed: U31.2 (-), U33.3 (VREFPS)
unnamed: U31.6 (-), U33.17 (VREFNS)
unnamed: U30.7, U32.16 (VREFNF)
unnamed: U30.1, U32.4 (VREFPF)
unnamed: U31.7, U33.16 (VREFNF)
unnamed: U31.1, U33.4 (VREFPF)
unnamed: U34.2 (-), U38.3 (VREFPS)
unnamed: U34.6 (-), U38.17 (VREFNS)
unnamed: U35.2 (-), U39.3 (VREFPS)
unnamed: U35.6 (-), U39.17 (VREFNS)
unnamed: U36.2 (-), U40.3 (VREFPS)
unnamed: U36.6 (-), U40.17 (VREFNS)
unnamed: U37.2 (-), U41.3 (VREFPS)
unnamed: U37.6 (-), U41.17 (VREFNS)
unnamed: U34.7, U38.16 (VREFNF)
unnamed: U34.1, U38.4 (VREFPF)
unnamed: U35.7, U39.16 (VREFNF)
unnamed: U35.1, U39.4 (VREFPF)
unnamed: U36.7, U40.16 (VREFNF)
unnamed: U36.1, U40.4 (VREFPF)
unnamed: U37.7, U41.16 (VREFNF)
unnamed: U37.1, U41.4 (VREFPF)
unnamed: U42.2 (-), U44.3 (VREFPS)
unnamed: U42.6 (-), U44.17 (VREFNS)
unnamed: U43.2 (-), U45.3 (VREFPS)
unnamed: U43.6 (-), U45.17 (VREFNS)
unnamed: U42.7, U44.16 (VREFNF)
unnamed: U42.1, U44.4 (VREFPF)
unnamed: U43.7, U45.16 (VREFNF)
unnamed: U43.1, U45.4 (VREFPF)
unnamed: U46.2 (-), U50.3 (VREFPS)
unnamed: U46.6 (-), U50.17 (VREFNS)
unnamed: U47.2 (-), U51.3 (VREFPS)
unnamed: U47.6 (-), U51.17 (VREFNS)
unnamed: U48.2 (-), U52.3 (VREFPS)
unnamed: U48.6 (-), U52.17 (VREFNS)
unnamed: U49.2 (-), U53.3 (VREFPS)
unnamed: U49.6 (-), U53.17 (VREFNS)
unnamed: U46.7, U50.16 (VREFNF)
unnamed: U46.1, U50.4 (VREFPF)
unnamed: U47.7, U51.16 (VREFNF)
unnamed: U47.1, U51.4 (VREFPF)
unnamed: U48.7, U52.16 (VREFNF)
unnamed: U48.1, U52.4 (VREFPF)
unnamed: U49.7, U53.16 (VREFNF)
unnamed: U49.1, U53.4 (VREFPF)
unnamed: U54.2 (-), U56.3 (VREFPS)
unnamed: U54.6 (-), U56.17 (VREFNS)
unnamed: U55.2 (-), U57.3 (VREFPS)
unnamed: U55.6 (-), U57.17 (VREFNS)
unnamed: U54.7, U56.16 (VREFNF)
unnamed: U54.1, U56.4 (VREFPF)
unnamed: U55.7, U57.16 (VREFNF)
unnamed: U55.1, U57.4 (VREFPF)
RESET_N: U10.6 (*RESET), U13.6 (*RESET), U15.6 (*RESET), U17.6 (*RESET), U19.6 (*RESET), U21.6 (*RESET), U26.6 (*RESET), U27.6 (*RESET), U28.6 (*RESET), U29.6 (*RESET), U32.6 (*RESET), U33.6 (*RESET), U38.6 (*RESET), U39.6 (*RESET), U40.6 (*RESET), U41.6 (*RESET), U44.6 (*RESET), U45.6 (*RESET), U50.6 (*RESET), U51.6 (*RESET), U52.6 (*RESET), U53.6 (*RESET), U56.6 (*RESET), U57.6 (*RESET), U100.11 (OUTE)
RESET_N_ALLCH: J12.19, J19.14, U100.6 (INE)
SCLK_CH1: J10.6, J18.4, U58.4 (INC)
SCLK_CH2: J10.16, J18.8, U83.4 (INC)
SCLK_CH3: J10.26, J18.12, U84.4 (INC)
SCLK_CH4: J9.29, J20.3, U85.4 (INC)
SCLK_CH5: J9.19, J20.7, U86.4 (INC)
SCLK_CH6: J9.9, J20.11, U87.4 (INC)
SCLK_CH7: J12.15, J14.14, U88.4 (INC)
SCLK_CH8: J5.21, J6.12, U89.4 (INC)
SCLK_CH9: J5.6, J6.10, U90.4 (INC)
SCLK_CH10: J7.4, J15.7, U91.4 (INC)
SCLK_CH11: J8.2, J15.2, U92.4 (INC)
SCLK_CH12: J6.5, J11.16, U93.4 (INC)
SCLK_CH13: J10.5, J17.3, U94.4 (INC)
SCLK_CH14: J10.15, J17.7, U95.4 (INC)
SCLK_CH15: J10.25, J17.11, U96.4 (INC)
SCLK_CH16: J9.26, J19.3, U97.4 (INC)
SCLK_CH17: J9.16, J19.7, U98.4 (INC)
SCLK_CH18: J9.6, J19.11, U99.4 (INC)
SCLK_CH19: J6.14, J12.13, U100.4 (INC)
SCLK_CH20: J4.12, J5.19, U101.4 (INC)
SCLK_CH21: J4.10, J5.4, U102.4 (INC)
SCLK_CH22: J7.7, J14.9, U103.4 (INC)
SCLK_CH23: J8.5, J14.4, U104.4 (INC)
SCLK_CH24: J6.4, J11.14, U105.4 (INC)
VCCN: C72.2, C74.2, C76.2, C78.2, C79.2, C80.2, C84.2, C85.2, C86.2, C90.2, C91.2, C92.2, C96.2, C97.2, C98.2, C102.2, C103.2, C104.2, C108.2, C109.2, C110.2, C114.2, C115.2, C116.2, J13.9, J13.11, J21.1, J21.2, J25.1, J26.1, U58.1 (VCC1), U83.1 (VCC1), U84.1 (VCC1), U85.1 (VCC1), U86.1 (VCC1), U87.1 (VCC1), U88.1 (VCC1), U89.1 (VCC1), U90.1 (VCC1), U91.1 (VCC1), U92.1 (VCC1), U93.1 (VCC1), U94.1 (VCC1), U95.1 (VCC1), U96.1 (VCC1), U97.1 (VCC1), U98.1 (VCC1), U99.1 (VCC1), U100.1 (VCC1), U101.1 (VCC1), U102.1 (VCC1), U103.1 (VCC1), U104.1 (VCC1), U105.1 (VCC1)
VDD: C1.1, C3.1, C5.1, C7.1, C9.1, C11.1, C13.1, C15.1, C46.1, C71.1, C120.1, C121.1, C122.1, C123.1, C130.1, C132.1, C134.1, C136.1, C138.1, C140.1, C142.1, C144.1, C146.1, C148.1, C150.1, C152.1, C154.1, C156.1, C158.1, C160.1, C162.1, C164.1, C166.1, C168.1, C170.1, C172.1, C174.1, C176.1, C178.1, C180.1, C182.1, C184.1, C186.1, C188.1, C190.1, C192.1, C194.1, C196.1, C198.1, C200.1, C202.1, C204.1, C206.1, C208.1, C210.1, C212.1, J1.1, J23.1, U1.1 (~SHDN), U1.2 (VIN), U2.1 (~SHDN), U2.2 (VIN), U3.1 (~SHDN), U3.2 (VIN), U4.1 (~SHDN), U4.2 (VIN), U5.1 (~SHDN), U5.2 (VIN), U6.1 (~SHDN), U6.2 (VIN), U7.1 (~SHDN), U7.2 (VIN), U8.1 (~SHDN), U8.2 (VIN), U9.8 (V+), U10.5 (VDD), U11.8 (V+), U12.8 (V+), U13.5 (VDD), U14.8 (V+), U15.5 (VDD), U16.8 (V+), U17.5 (VDD), U18.8 (V+), U19.5 (VDD), U20.8 (V+), U21.5 (VDD), U22.8 (V+), U23.8 (V+), U24.8 (V+), U25.8 (V+), U26.5 (VDD), U27.5 (VDD), U28.5 (VDD), U29.5 (VDD), U30.8 (V+), U31.8 (V+), U32.5 (VDD), U33.5 (VDD), U34.8 (V+), U35.8 (V+), U36.8 (V+), U37.8 (V+), U38.5 (VDD), U39.5 (VDD), U40.5 (VDD), U41.5 (VDD), U42.8 (V+), U43.8 (V+), U44.5 (VDD), U45.5 (VDD), U46.8 (V+), U47.8 (V+), U48.8 (V+), U49.8 (V+), U50.5 (VDD), U51.5 (VDD), U52.5 (VDD), U53.5 (VDD), U54.8 (V+), U55.8 (V+), U56.5 (VDD), U57.5 (VDD), U59.7 (V+), U60.7 (V+), U61.7 (V+), U62.7 (V+), U63.7 (V+), U64.7 (V+), U65.7 (V+), U66.7 (V+), U67.7 (V+), U68.7 (V+), U69.7 (V+), U70.7 (V+), U71.7 (V+), U72.7 (V+), U73.7 (V+), U74.7 (V+), U75.7 (V+), U76.7 (V+), U77.7 (V+), U78.7 (V+), U79.7 (V+), U80.7 (V+), U81.7 (V+), U82.7 (V+)
VOUT_F1: C2.1, R1.1, U1.6 (VOUT_S), U1.7 (VOUT_F)
VOUT_F2: C4.1, R2.1, U2.6 (VOUT_S), U2.7 (VOUT_F)
VOUT_F3: C6.1, R3.1, U3.6 (VOUT_S), U3.7 (VOUT_F)
VOUT_F4: C8.1, R4.1, U4.6 (VOUT_S), U4.7 (VOUT_F)
VOUT_F5: C10.1, R5.1, U5.6 (VOUT_S), U5.7 (VOUT_F)
VOUT_F6: C12.1, R6.1, U6.6 (VOUT_S), U6.7 (VOUT_F)
VOUT_F7: C14.1, R7.1, U7.6 (VOUT_S), U7.7 (VOUT_F)
VOUT_F8: C16.1, R8.1, U8.6 (VOUT_S), U8.7 (VOUT_F)
VREF+: C21.1, J23.4, R14.2, U11.3 (+), U12.3 (+), U14.3 (+), U16.3 (+), U18.3 (+), U20.3 (+), U22.3 (+), U23.3 (+), U24.3 (+), U25.3 (+), U30.3 (+), U31.3 (+), U34.3 (+), U35.3 (+), U36.3 (+), U37.3 (+), U42.3 (+), U43.3 (+), U46.3 (+), U47.3 (+), U48.3 (+), U49.3 (+), U54.3 (+), U55.3 (+)
VREF-: C19.1, J23.5, R12.2, U11.5 (+), U12.5 (+), U14.5 (+), U16.5 (+), U18.5 (+), U20.5 (+), U22.5 (+), U23.5 (+), U24.5 (+), U25.5 (+), U30.5 (+), U31.5 (+), U34.5 (+), U35.5 (+), U36.5 (+), U37.5 (+), U42.5 (+), U43.5 (+), U46.5 (+), U47.5 (+), U48.5 (+), U49.5 (+), U54.5 (+), U55.5 (+)
VSS: C124.1, C125.1, C126.1, C127.1, C128.1, C129.1, C131.1, C133.1, C135.1, C137.1, C139.1, C141.1, C143.1, C145.1, C147.1, C149.1, C151.1, C153.1, C155.1, C157.1, C159.1, C161.1, C163.1, C165.1, C167.1, C169.1, C171.1, C173.1, C175.1, C177.1, C179.1, C181.1, C183.1, C185.1, C187.1, C189.1, C191.1, C193.1, C195.1, C197.1, C199.1, C201.1, C203.1, C205.1, C207.1, C209.1, C211.1, C213.1, J1.3, J23.3, U9.4 (V-), U10.18 (VSS), U11.4 (V-), U12.4 (V-), U13.18 (VSS), U14.4 (V-), U15.18 (VSS), U16.4 (V-), U17.18 (VSS), U18.4 (V-), U19.18 (VSS), U20.4 (V-), U21.18 (VSS), U22.4 (V-), U23.4 (V-), U24.4 (V-), U25.4 (V-), U26.18 (VSS), U27.18 (VSS), U28.18 (VSS), U29.18 (VSS), U30.4 (V-), U31.4 (V-), U32.18 (VSS), U33.18 (VSS), U34.4 (V-), U35.4 (V-), U36.4 (V-), U37.4 (V-), U38.18 (VSS), U39.18 (VSS), U40.18 (VSS), U41.18 (VSS), U42.4 (V-), U43.4 (V-), U44.18 (VSS), U45.18 (VSS), U46.4 (V-), U47.4 (V-), U48.4 (V-), U49.4 (V-), U50.18 (VSS), U51.18 (VSS), U52.18 (VSS), U53.18 (VSS), U54.4 (V-), U55.4 (V-), U56.18 (VSS), U57.18 (VSS), U59.4 (V-), U60.4 (V-), U61.4 (V-), U62.4 (V-), U63.4 (V-), U64.4 (V-), U65.4 (V-), U66.4 (V-), U67.4 (V-), U68.4 (V-), U69.4 (V-), U70.4 (V-), U71.4 (V-), U72.4 (V-), U73.4 (V-), U74.4 (V-), U75.4 (V-), U76.4 (V-), U77.4 (V-), U78.4 (V-), U79.4 (V-), U80.4 (V-), U81.4 (V-), U82.4 (V-)
